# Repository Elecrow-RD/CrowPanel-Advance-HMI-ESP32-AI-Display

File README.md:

Here is the CrowPanel-Advance-HMI-ESP32-AI-Display series screen program schematic datasheet and other information, you can download the corresponding information according to your own screen size, select the branch section.

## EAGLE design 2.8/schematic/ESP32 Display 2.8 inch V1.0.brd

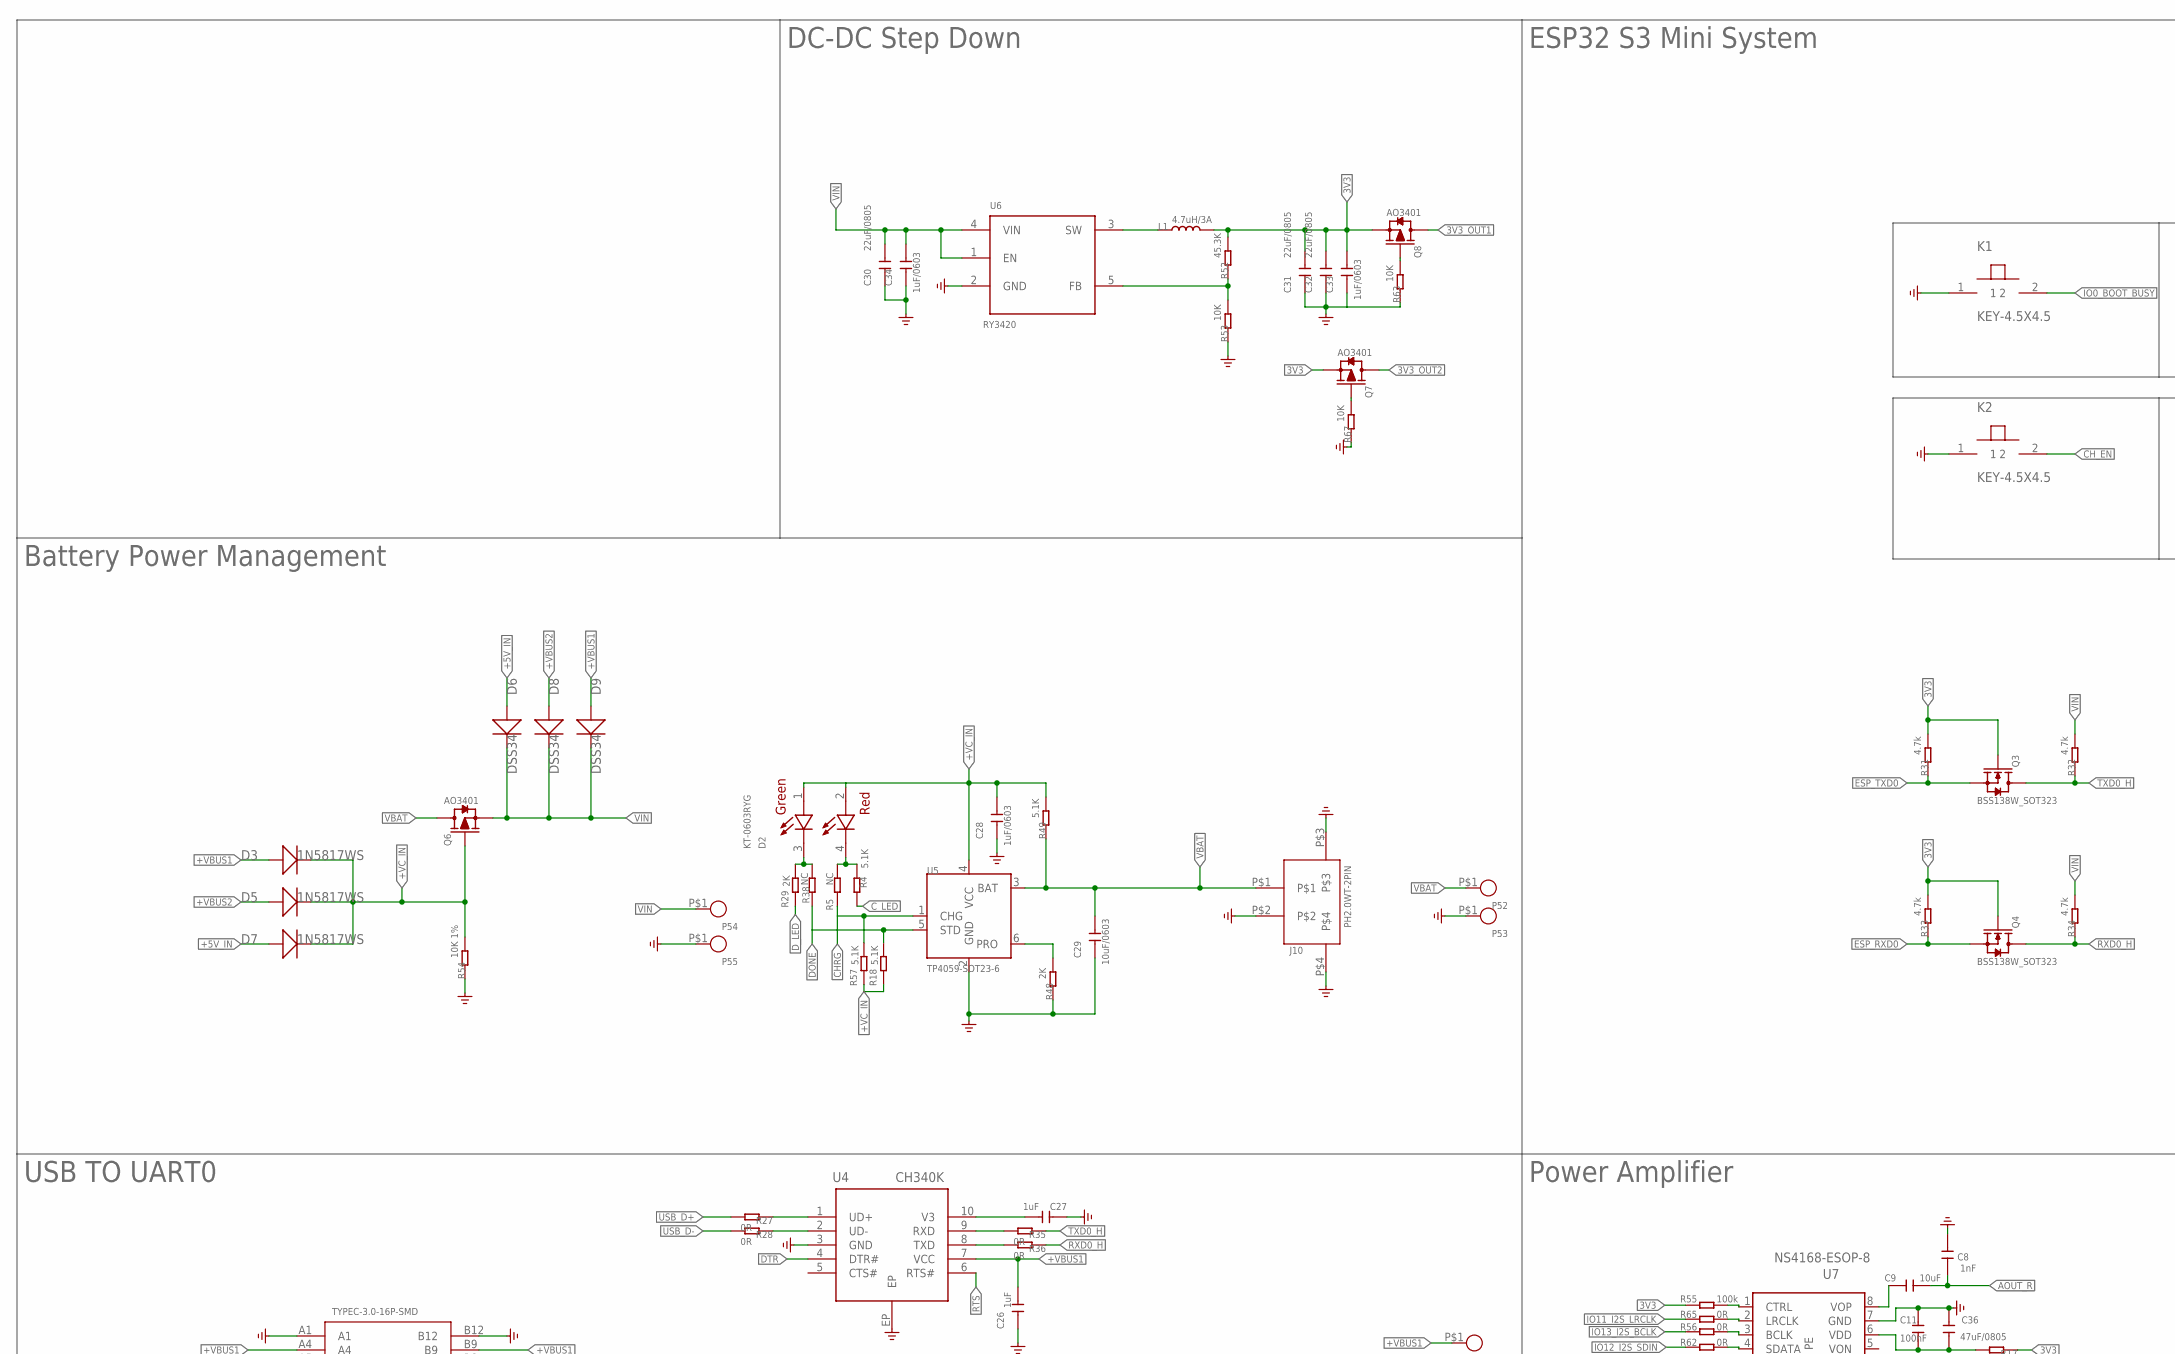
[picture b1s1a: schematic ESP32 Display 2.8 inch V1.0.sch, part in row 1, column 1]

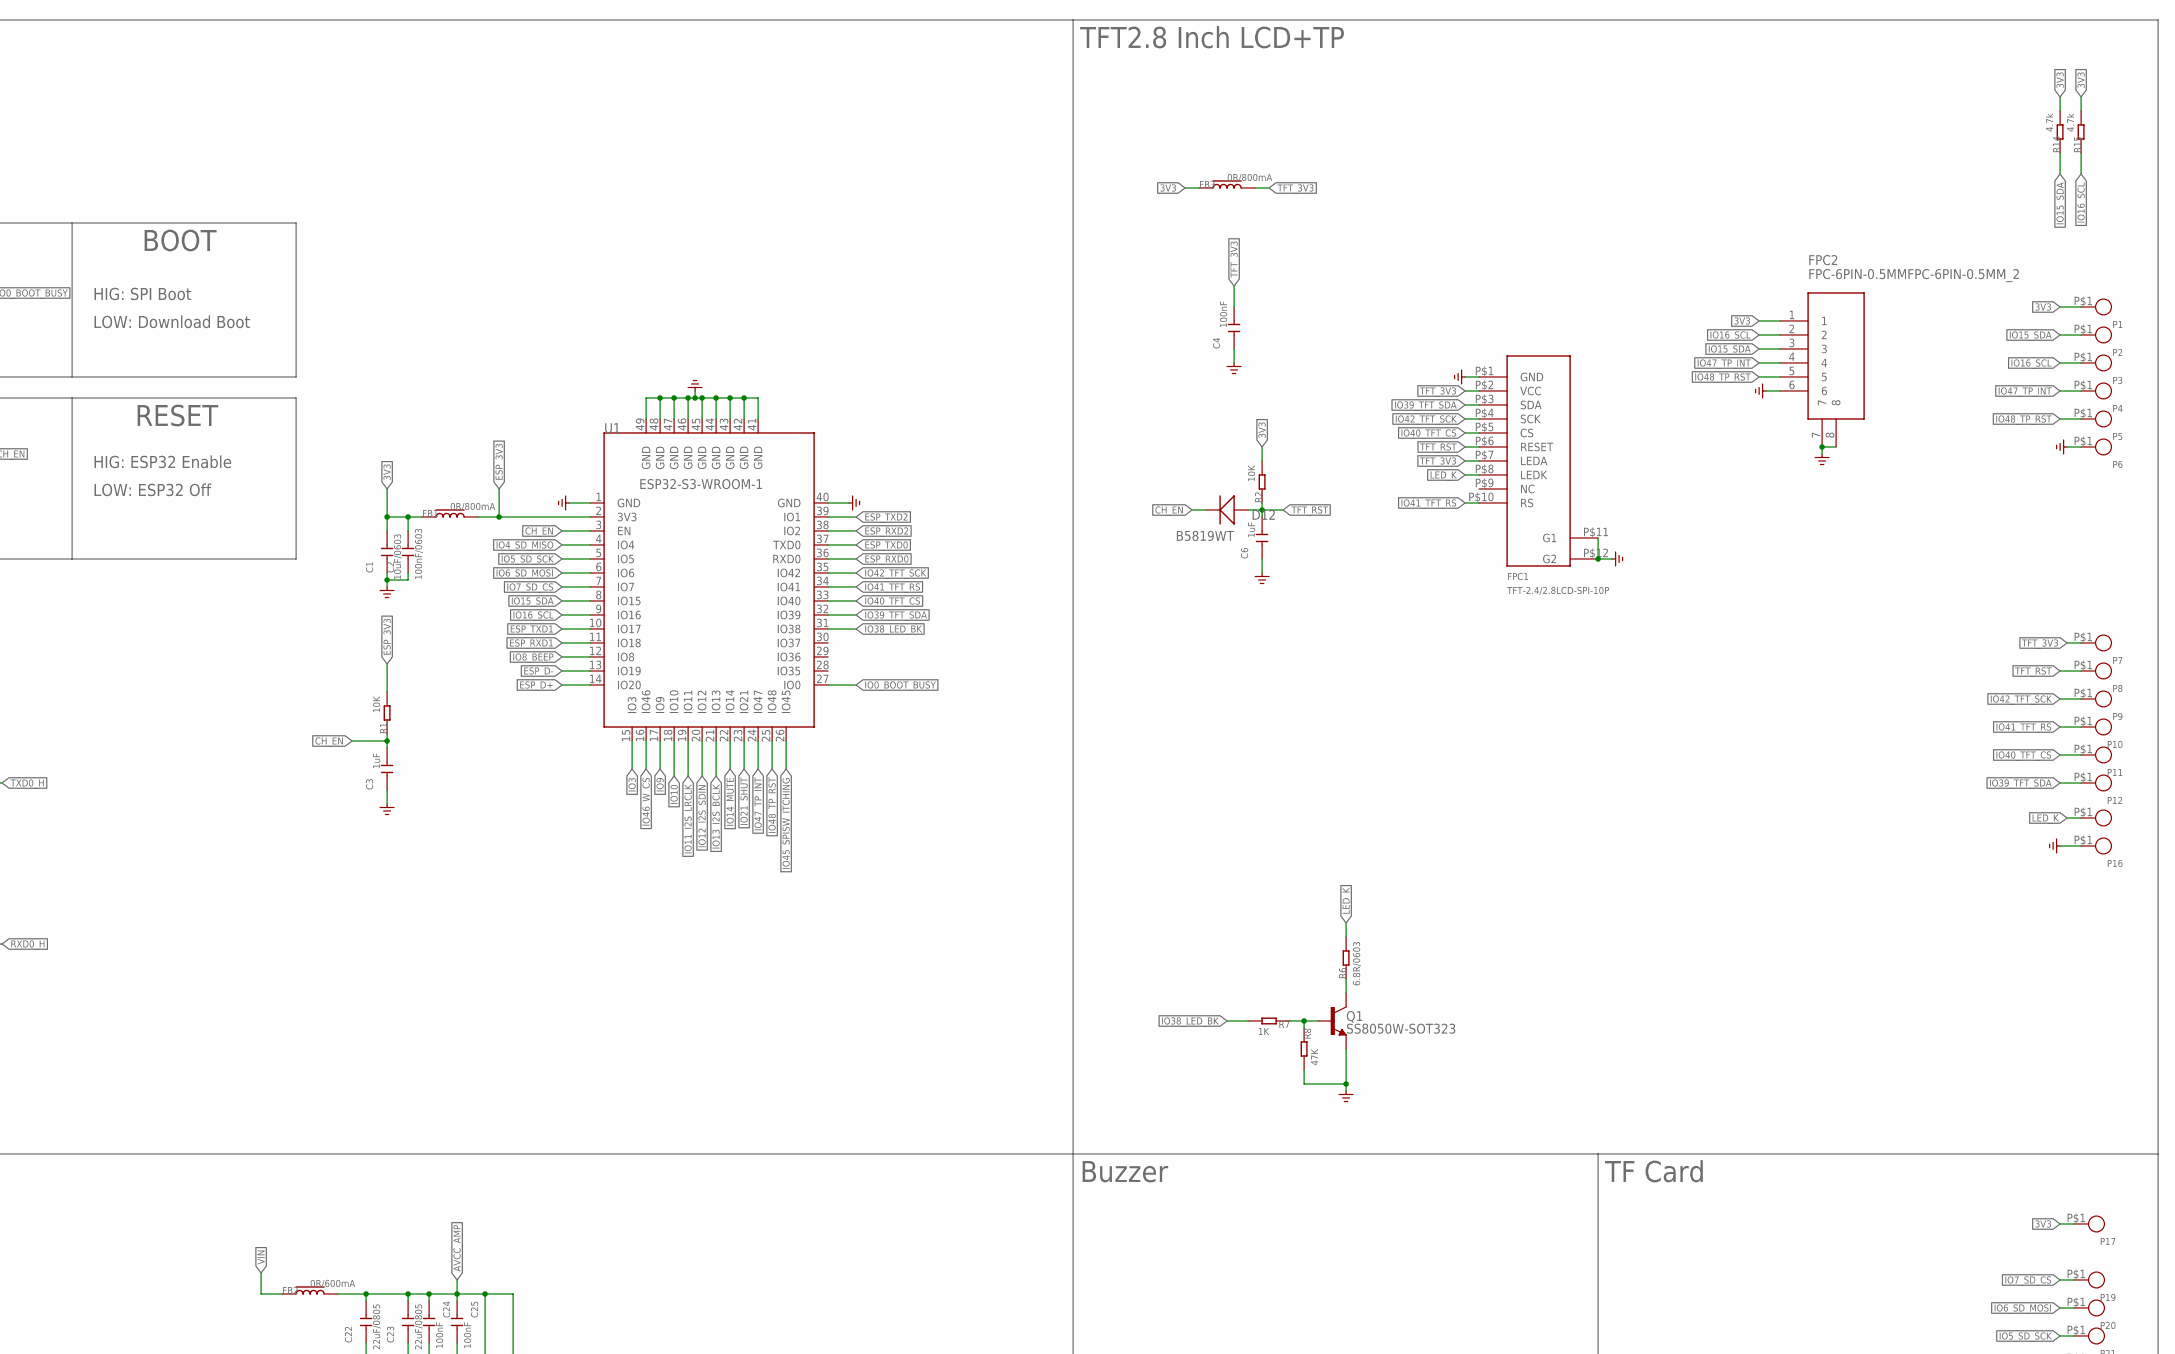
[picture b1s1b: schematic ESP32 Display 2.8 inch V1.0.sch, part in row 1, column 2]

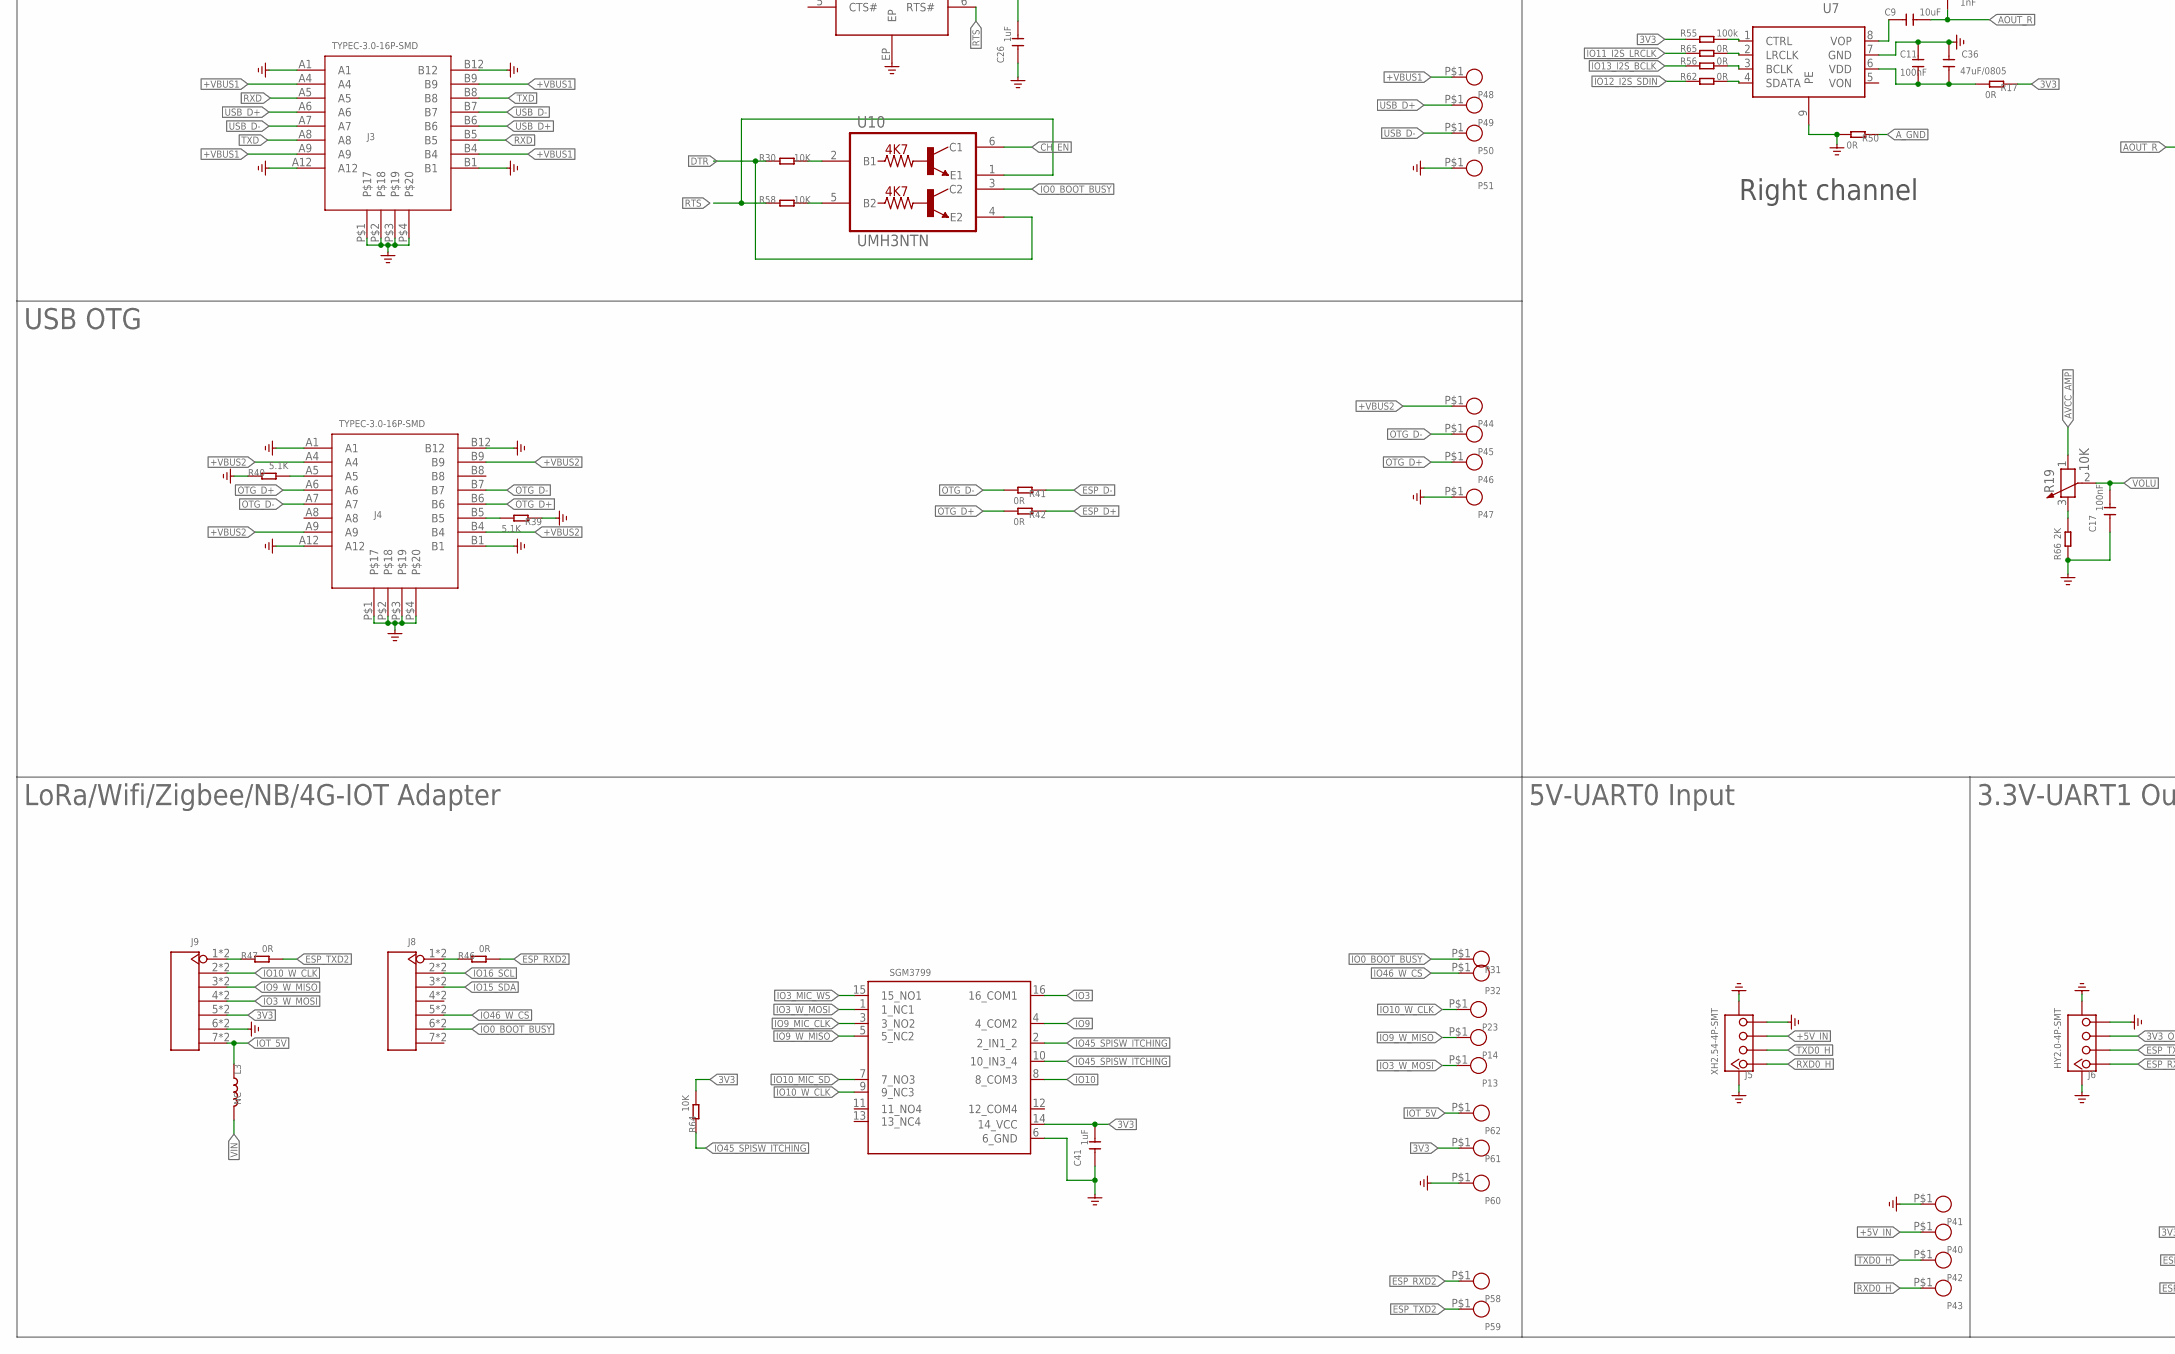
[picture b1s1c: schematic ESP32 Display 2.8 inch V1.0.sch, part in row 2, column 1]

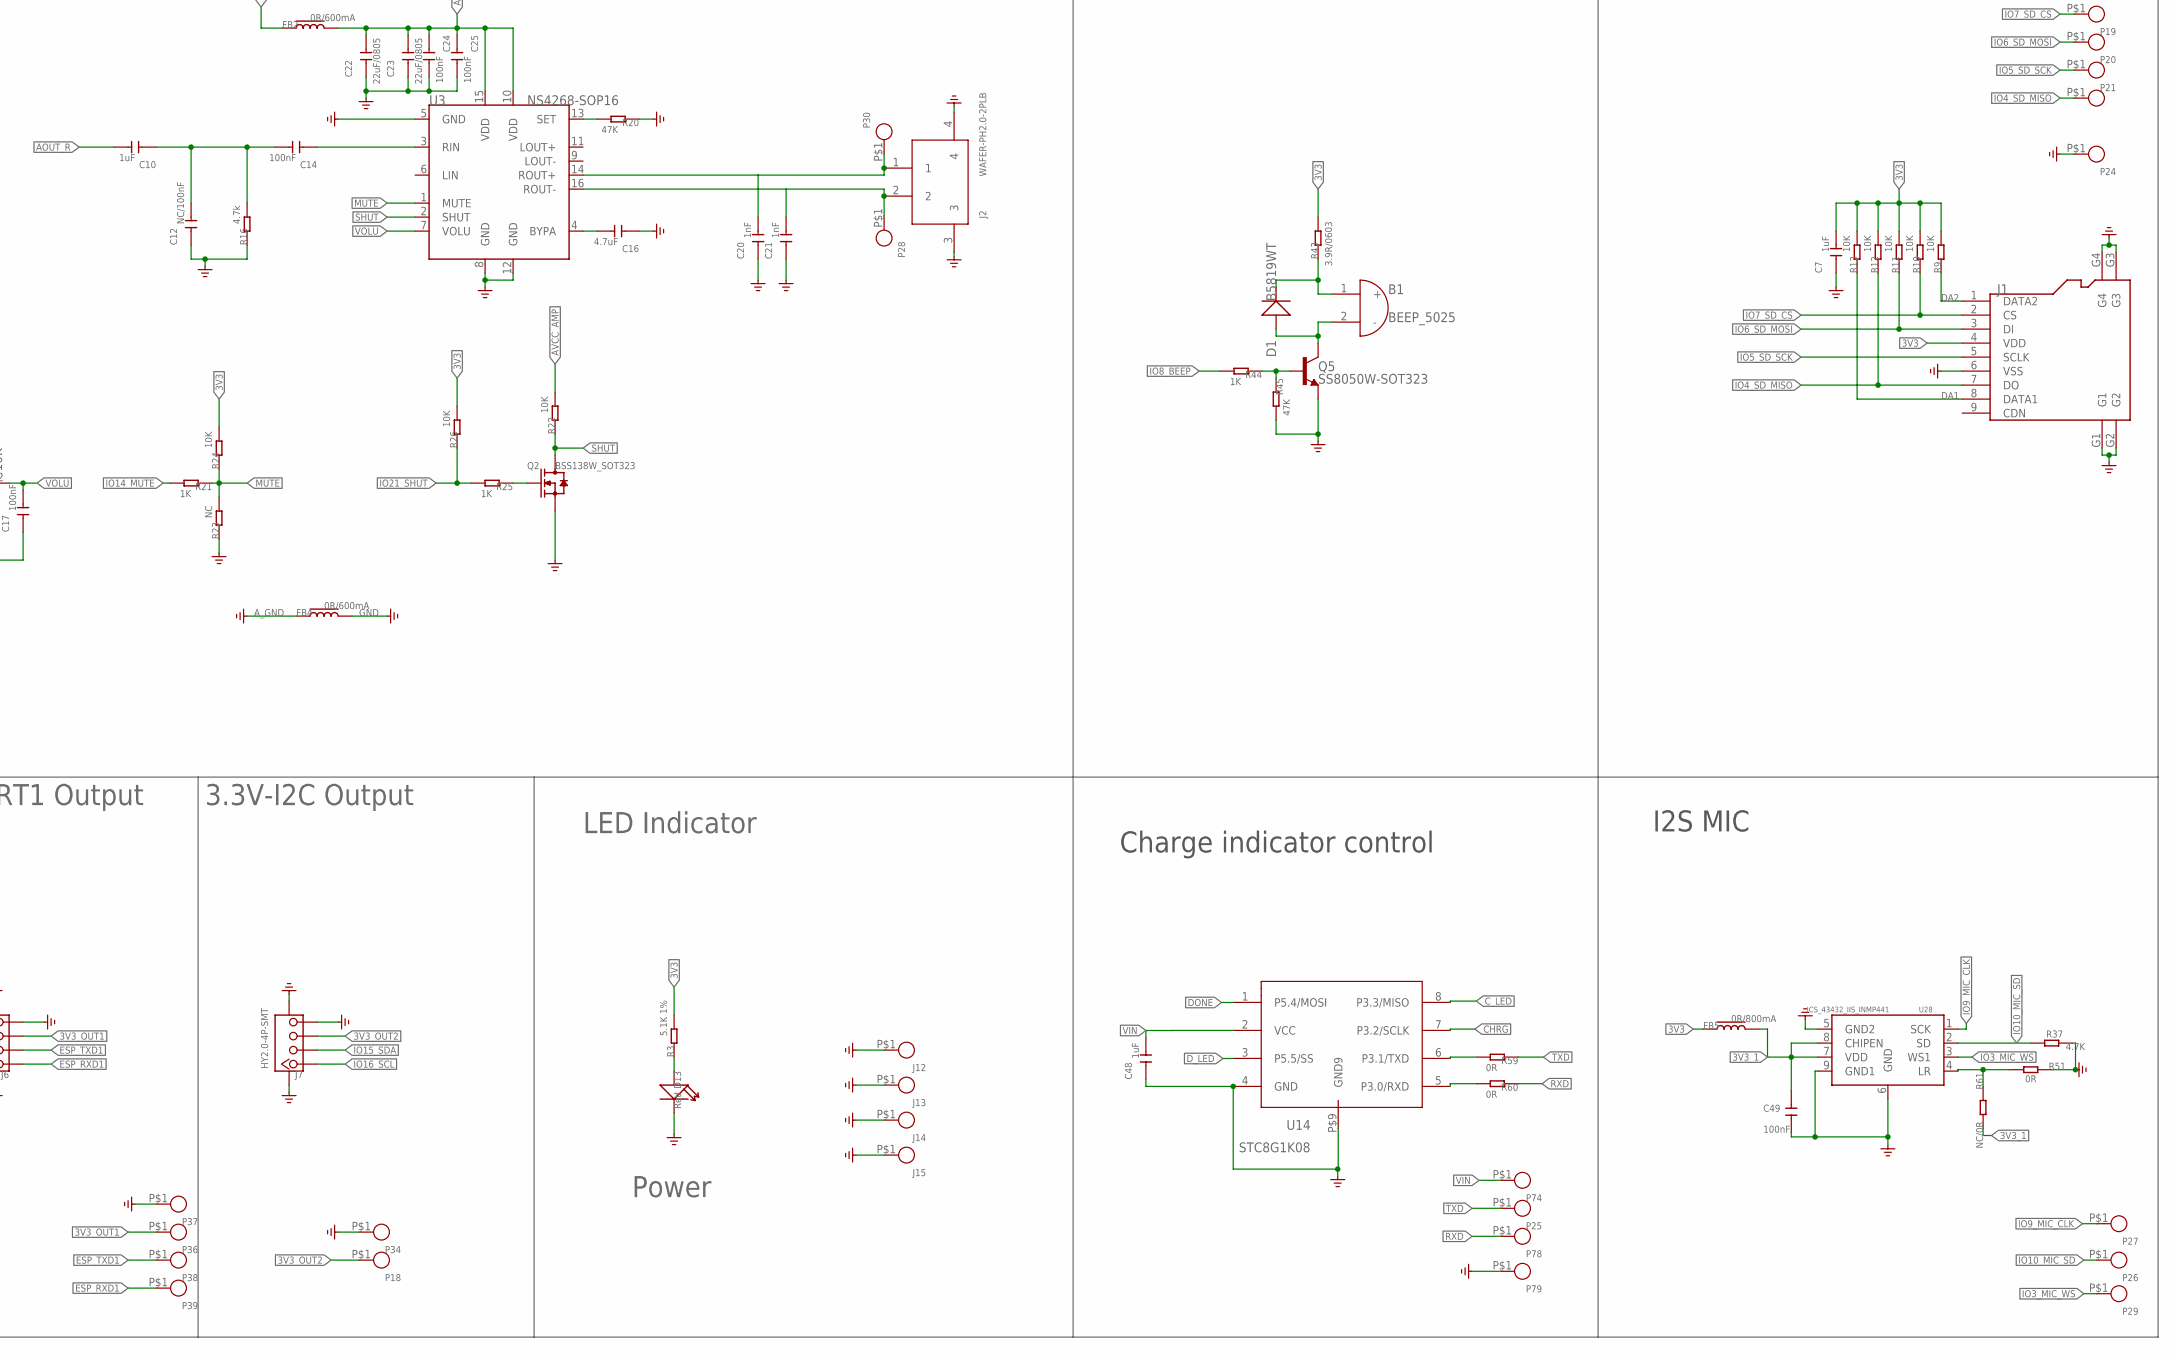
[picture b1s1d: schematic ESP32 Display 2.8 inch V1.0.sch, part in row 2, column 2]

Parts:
B1: BEEP_5025
C1, C29: 10uF/0603; C0603
C2: 100nF/0603; C0603
C3, C6, C7, C10, C26, C27, C41, C48: 1uF; C0402
C4, C11, C14, C17, C24, C25: 100nF; C0402
C8, C20, C21: 1nF; C0402
C9: 10uF; C0402
C12: NC/100nF; C0402
C16: 4.7uF; C0402
C22, C23, C30, C31, C32: 22uF/0805; C0805
C28, C33, C34: 1uF/0603; C0603
C36: 47uF/0805; C0805
C49: 100nF; C0603
D1, D12: B5819WT; D_SOD523
D2: KT-0603RYG; LED_KT-0603RYG
D3, D5, D7: 1N5817WS; D_SOD323
D6, D8, D9: DSS34; D_SOD123FL
D13: Red; LED0603
FB1, FB3, FB5: 0R/800mA; L0603
FB2, FB4: 0R/600mA; L0603
FPC1: TFT-2.4/2.8LCD-SPI-10P; FPC-P0.5MM-10P-SMD
FPC2: FPC-6PIN-0.5MMFPC-6PIN-0.5MM_2; FPC-6PIN-0.5MM_2
J1: HOLDER-MICROSD-9P; 9P-SMD-W/-RING
J2: WAFER-PH2.0-2PLB; CONN-TH_2P-P2.00_XUNPU_WAFER-PH2.0-2PLB
J3, J4: TYPEC-3.0-16P-SMD; USB-3.0TYPEC-SMD
J5: XH2.54-4P-SMT; XH2.54-4P-SMD
J6, J7: HY2.0-4P-SMT; CONNECTOR_4P-SMD-2.0
J8, J9: HEADER-7P-18.28X2.5; H7-2.54-18.28X2.5X5MM
J10: PH2.0WT-2PIN
J12, J13, J14, J15: THO-M3.25MM-HOLE; THO-M3.2*5MM-HOLE
K1, K2: KEY-4.5X4.5; KEY-4.5X4.5-SMD
L1: 4.7uH/3A; L0420
L3: NC; L0603
P1, P2, P3, P4, P5, P6, P7, P8, P9, P10, P11, P12, P13, P14, P15, P16, P17, P18, P19, P20, P21, P22, P23, P24, P25, P26, P27, P28, P29, P30, P31, P32, P34, P36, P37, P38, P39, P40, P41, P42, P43, P44, P45, P46, P47, P48, P49, P50, P51, P52, P53, P54, P55, P58, P59, P60, P61, P62, P74, P78, P79: TEST_PADPAD-1.5MM; TEST_PAD-1.5MM
Q1, Q5: SS8050W-SOT323; MOS_SOT323
Q2, Q3, Q4: BSS138W_SOT323; MOS_SOT323
Q6, Q7, Q8: AO3401; PMOS_SOT23
R1, R2, R9, R10, R11, R12, R13, R22, R24, R26, R30, R53, R58, R63, R64, R67: 10K; R0402
R3: 5.1K 1%; R0402
R4, R18, R39, R40, R49, R57: 5.1K; R0402
R5, R23, R38: NC; R0402
R6: 6.8R/0603; R0603-SP
R7, R21, R25, R44: 1K; R0402
R8, R20, R45: 47K; R0402
R14, R15, R16, R31, R32, R33, R34: 4.7k; R0402
R17, R27, R28, R35, R36, R41, R42, R46, R47, R50, R56, R59, R60, R62, R65: 0R; R0402
R19: 10K; 3P-SMD-SQUA-3.6X3.3
R29, R48, R66: 2K; R0402
R37: 4.7K; R0603-SP
R43: 3.9R/0603; R0603-SP
R51: 0R; R0603-SP
R52: 45.3K; R0402
R54: 10K 1%; R0402
R55: 100k; R0402
R61: NC/0R; R0603-SP
U1: ESP32-S3-WROOM-1; ESP32-S3-WROOM-1-SMD41
U3: NS4268-SOP16; SOP-16
U4: CH340K; ESOP-10-EP-150MIL
U5: TP4059-SOT23-6; SOT23-6L
U6: RY3420; IC_SOT23-5
U7: NS4168-ESOP-8
U8: SGM3799; IC_SGM3799_TQFN2.6X1.8_16L
U10: UMH3NTN; SOP65P210X100-6N
U14: STC8G1K08; DFN8
U28: ICS_43432_IIS_INMP441

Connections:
3V3: C1.2, C2.2, C7.2, C31.2, C32.2, C33.2, C41.2, FB1.1, FB3.1, FB5.1, FPC2.1, J1.4 (VDD), J9.5, J9.5-5 (5), L1.2, P1.P$1, P17.P$1, P61.P$1, Q3.1 (G), Q4.1 (G), Q7.2 (S), Q8.2 (S), R2.2, R3.2, R9.2, R10.2, R11.2, R12.2, R13.2, R14.2, R15.2, R17.1, R24.2, R26.2, R31.2, R33.2, R43.2, R52.2, R55.2, R64.2, U8.14 (14_VCC)
3V3_1: C49.2, FB5.2, R61.2, U28.7 (VDD), U28.8 (CHIPEN)
3V3_OUT1: J6.3, P36.P$1, Q8.3 (D)
3V3_OUT2: J7.3, P18.P$1, Q7.3 (D)
+5V_IN: D6.+, D7.+, J5.3, P40.P$1
+VBUS1: C26.2, D3.+, D9.+, J3.A4, J3.A9, J3.B4, J3.B9, P48.P$1, U4.7 (VCC)
+VBUS2: D5.+, D8.+, J4.A4, J4.A9, J4.B4, J4.B9, P44.P$1
+VC_IN: C28.2, D2.1, D2.2, D3.-, D5.-, D7.-, Q6.1 (G), R18.1, R49.2, R54.2, R57.1, U5.4 (VCC)
AOUT_R: C8.2, C9.2, C10.2
AVCC_AMP: C22.2, C23.2, C24.1, C25.1, FB2.2, R19.1, R22.2, U3.10 (VDD), U3.15 (VDD)
A_GND: C12.1, C16.1, C17.1, C20.1, C21.1, C22.1, C23.1, C24.2, C25.2, FB4.1, J2.3, J2.4, Q2.2 (S), R16.1, R20.1, R23.1, R50.1, R66.1, U3.5 (GND), U3.8 (GND), U3.12 (GND)
CHRG: R5.1, R57.2, U5.1 (CHG), U14.7 (P3.2/SCLK)
CH_EN: C3.2, D12.-, K2.2, R1.1, U1.3 (EN), U10.6 (C1)
C_LED: R4.1, U14.8 (P3.3/MISO)
DA1: J1.8 (DATA1), R13.1
DA2: J1.1 (DATA2), R9.1
DONE: R18.2, R38.1, U5.5 (STD), U14.1 (P5.4/MOSI)
DTR: R30.2, U4.4 (DTR#), U10.4 (E2)
D_LED: R29.1, U14.3 (P5.5/SS)
ESP_3V3: FB1.2, R1.2, U1.2 (3V3)
ESP_D+: R42.1, U1.14 (IO20)
ESP_D-: R41.1, U1.13 (IO19)
ESP_RXD0: Q4.2 (S), R33.1, U1.36 (RXD0)
ESP_RXD1: J6.1, P39.P$1, U1.11 (IO18)
ESP_RXD2: P58.P$1, R46.2, U1.38 (IO2)
ESP_TXD0: Q3.2 (S), R31.1, U1.37 (TXD0)
ESP_TXD1: J6.2, P38.P$1, U1.10 (IO17)
ESP_TXD2: P59.P$1, R47.2, U1.39 (IO1)
GND: C1.1, C2.1, C3.1, C4.1, C6.1, C7.1, C8.1, C11.2, C26.1, C27.1, C28.1, C29.1, C30.1, C31.1, C32.1, C33.1, C34.1, C36.2, C41.1, C48.1, C49.1, D13.-, FB4.2, FPC1.P$1 (GND), FPC1.P$11 (G1), FPC1.P$12 (G2), FPC2.6, FPC2.7, FPC2.8, J1.6 (VSS), J1.G1, J1.G2, J1.G3, J1.G4, J3.A1, J3.A12, J3.B1, J3.B12, J3.P$1, J3.P$2, J3.P$3, J3.P$4, J4.A1, J4.A12, J4.B1, J4.B12, J4.P$1, J4.P$2, J4.P$3, J4.P$4, J5.4, J5.5 (SS1), J5.6 (SS2), J6.4, J6.SS1, J6.SS2, J7.4, J7.SS1, J7.SS2, J9.6, J9.6-6 (6), J10.P$2, J10.P$3, J10.P$4, J12.P$1, J13.P$1, J14.P$1, J15.P$1, K1.1, K2.1, P6.P$1, P16.P$1, P24.P$1, P34.P$1, P37.P$1, P41.P$1, P47.P$1, P51.P$1, P53.P$1, P55.P$1, P60.P$1, P79.P$1, Q1.2 (E), Q5.2 (E), R8.2, R37.2, R39.1, R40.1, R45.2, R48.1, R50.2, R51.1, R53.1, R54.1, R63.1, R67.1, U1.1 (GND), U1.40 (GND), U1.41 (GND), U1.42 (GND), U1.43 (GND), U1.44 (GND), U1.45 (GND), U1.46 (GND), U1.47 (GND), U1.48 (GND), U1.49 (GND), U4.3 (GND), U4.EP, U5.2 (GND), U6.2 (GND), U7.7 (GND), U7.9 (PE), U8.6 (6_GND), U14.4 (GND), U14.P$9 (GND9), U28.5 (GND2), U28.6 (GND), U28.9 (GND1)
IO0_BOOT_BUSY: J8.6, J8.6-6 (6), K1.2, P31.P$1, U1.27 (IO0), U10.3 (C2)
IO3: U1.15 (IO3), U8.16 (16_COM1)
IO3_MIC_WS: P29.P$1, U8.15 (15_NO1), U28.3 (WS1)
IO3_W_MOSI: J9.4, J9.4-4 (4), P13.P$1, U8.1 (1_NC1)
IO4_SD_MISO: J1.7 (DO), P22.P$1, R12.1, U1.4 (IO4)
IO5_SD_SCK: J1.5 (SCLK), P21.P$1, U1.5 (IO5)
IO6_SD_MOSI: J1.3 (DI), P20.P$1, R11.1, U1.6 (IO6)
IO7_SD_CS: J1.2 (CS), P19.P$1, R10.1, U1.7 (IO7)
IO8_BEEP: R44.2, U1.12 (IO8)
IO9: U1.17 (IO9), U8.4 (4_COM2)
IO9_MIC_CLK: P27.P$1, U8.3 (3_NO2), U28.1 (SCK)
IO9_W_MISO: J9.3, J9.3-3 (3), P14.P$1, U8.5 (5_NC2)
IO10: U1.18 (IO10), U8.8 (8_COM3)
IO10_MIC_SD: P26.P$1, R37.1, U8.7 (7_NO3), U28.2 (SD)
IO10_W_CLK: J9.2, J9.2-2 (2), P23.P$1, U8.9 (9_NC3)
IO11_I2S_LRCLK: R65.2, U1.19 (IO11)
IO12_I2S_SDIN: R62.2, U1.20 (IO12)
IO13_I2S_BCLK: R56.2, U1.21 (IO13)
IO14_MUTE: R21.2, U1.22 (IO14)
IO15_SDA: FPC2.3, J7.2, J8.3, J8.3-3 (3), P2.P$1, R14.1, U1.8 (IO15)
IO16_SCL: FPC2.2, J7.1, J8.2, J8.2-2 (2), P3.P$1, R15.1, U1.9 (IO16)
IO21_SHUT: R25.2, R26.1, U1.23 (IO21)
IO38_LED_BK: R7.2, U1.31 (IO38)
IO39_TFT_SDA: FPC1.P$3 (SDA), P12.P$1, U1.32 (IO39)
IO40_TFT_CS: FPC1.P$5 (CS), P11.P$1, U1.33 (IO40)
IO41_TFT_RS: FPC1.P$10 (RS), P10.P$1, U1.34 (IO41)
IO42_TFT_SCK: FPC1.P$4 (SCK), P9.P$1, U1.35 (IO42)
IO45_SPISW_ITCHING: R64.1, U1.26 (IO45), U8.2 (2_IN1_2), U8.10 (10_IN3_4)
IO46_W_CS: J8.5, J8.5-5 (5), P32.P$1, U1.16 (IO46)
IO47_TP_INT: FPC2.4, P4.P$1, U1.24 (IO47)
IO48_TP_RST: FPC2.5, P5.P$1, U1.25 (IO48)
IOT_5V: J9.7, J9.7-7 (7), L3.1, P62.P$1
LED_K: FPC1.P$8 (LEDK), P15.P$1, R6.2
MUTE: R21.1, R23.2, R24.1, U3.1 (MUTE)
unnamed: Q1.3 (C), R6.1
unnamed: D13.+, R3.1
unnamed: Q1.1 (B), R7.1, R8.1
unnamed: D2.3, R29.2, R38.2
unnamed: D2.4, R4.2, R5.2
unnamed: R55.1, U7.1 (CTRL)
unnamed: C14.1, U3.3 (RIN)
unnamed: R65.1, U7.2 (LRCLK)
unnamed: C10.1, C12.2, C14.2, R16.2
unnamed: R51.2, R61.1, U28.4 (LR)
unnamed: R20.2, U3.13 (SET)
unnamed: C16.2, U3.4 (BYPA)
unnamed: Q2.1 (G), R25.1
unnamed: R27.1, U4.1 (UD+)
unnamed: R28.1, U4.2 (UD-)
unnamed: L1.1, U6.3 (SW)
unnamed: R30.1, U10.2 (B1)
unnamed: R58.1, U10.5 (B2)
unnamed: R59.2, U14.6 (P3.1/TXD)
unnamed: C27.2, U4.10 (V3)
unnamed: R60.2, U14.5 (P3.0/RXD)
unnamed: R35.2, U4.9 (RXD)
unnamed: R36.2, U4.8 (TXD)
unnamed: J9.1, J9.1-1 (1), R47.1
unnamed: J4.B5, R39.2
unnamed: J4.A5, R40.2
unnamed: Q5.1 (B), R44.1, R45.1
unnamed: B1.2 (-), D1.+, Q5.3 (C)
unnamed: B1.1 (+), D1.-, R43.1
unnamed: R19.3 (2), R66.2
unnamed: R52.1, R53.2, U6.5 (FB)
unnamed: R48.2, U5.6 (PRO)
unnamed: J8.1, J8.1-1 (1), R46.1
unnamed: Q8.1 (G), R63.2
unnamed: Q7.1 (G), R67.2
unnamed: R56.1, U7.3 (BCLK)
unnamed: R62.1, U7.4 (SDATA)
unnamed: C11.1, C36.1, R17.2, U7.6 (VDD)
unnamed: C9.1, U7.8 (VOP)
OTG_D+: J4.A6, J4.B6, P46.P$1, R42.2
OTG_D-: J4.A7, J4.B7, P45.P$1, R41.2
ROUT+: C20.2, J2.1, P30.P$1, U3.14 (ROUT+)
ROUT-: C21.2, J2.2, P28.P$1, U3.16 (ROUT-)
RTS: R58.2, U4.6 (RTS#), U10.1 (E1)
RXD: J3.A5, J3.B5, P78.P$1, R60.1
RXD0_H: J5.1, P43.P$1, Q4.3 (D), R34.1, R36.1
SHUT: Q2.3 (D), R22.1, U3.2 (SHUT)
TFT_3V3: C4.2, FB3.2, FPC1.P$2 (VCC), FPC1.P$7 (LEDA), P7.P$1
TFT_RST: C6.2, D12.+, FPC1.P$6 (RESET), P8.P$1, R2.1
TXD: J3.A8, J3.B8, P25.P$1, R59.1
TXD0_H: J5.2, P42.P$1, Q3.3 (D), R32.1, R35.1
USB_D+: J3.A6, J3.B6, P49.P$1, R27.2
USB_D-: J3.A7, J3.B7, P50.P$1, R28.2
VBAT: C29.2, J10.P$1, P52.P$1, Q6.3 (D), R49.1, U5.3 (BAT)
VIN: C30.2, C34.2, C48.2, D6.-, D8.-, D9.-, FB2.1, L3.2, P54.P$1, P74.P$1, Q6.2 (S), R32.2, R34.2, U6.1 (EN), U6.4 (VIN), U14.2 (VCC)
VOLU: C17.2, R19.2 (3), U3.7 (VOLU)

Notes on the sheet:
DC-DC Step Down
Battery Power Management
USB TO UART0
USB OTG
LoRa/Wifi/Zigbee/NB/4G-IOT Adapter
5V-UART0 Input
3.3V-UART1 Output
3.3V-I2C Output
Power Amplifier
ESP32 S3 Mini System
TFT2.8 Inch LCD+TP
Buzzer
TF Card
LED Indicator
Power
BOOT
RESET
HIG: SPI Boot
LOW: Download Boot
HIG: ESP32 Enable
LOW: ESP32 Off
Charge indicator control
I2S MIC
Right channel

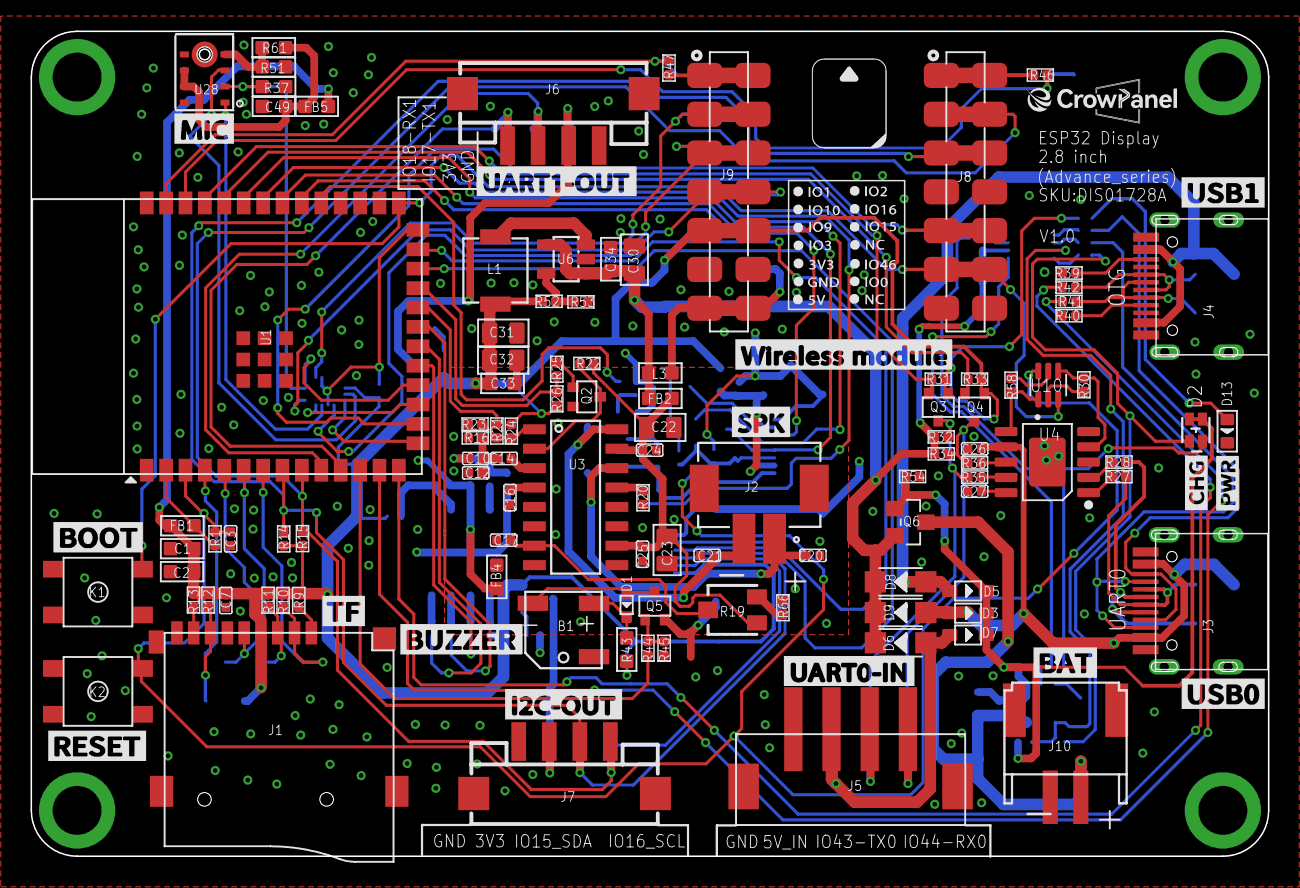
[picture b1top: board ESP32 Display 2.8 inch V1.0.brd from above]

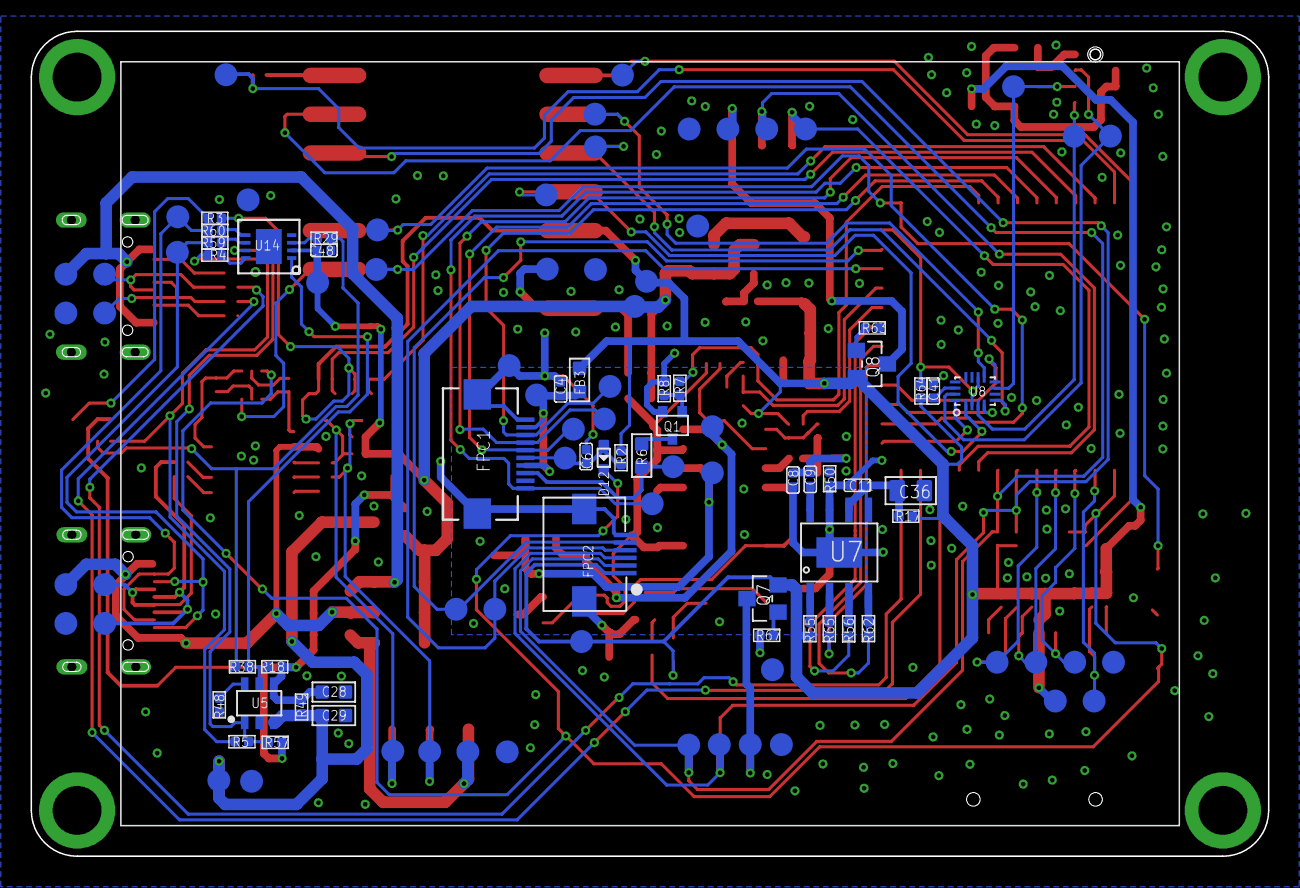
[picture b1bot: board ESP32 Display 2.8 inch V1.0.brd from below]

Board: 2 copper layers, 81.0 x 54.0 mm, 215 parts (107 on the bottom side), 119 nets.
